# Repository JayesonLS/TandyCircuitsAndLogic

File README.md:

TandyCircuitsAndLogic
=====================

Circuits and programmable Logic for use with Tandy computers.

See the main source file (.pld for WinCUPL projects) in each folder for 
specific details. Check that the compiled file (.jed) is up to date
(committed at the same time or later than the most recent source changes)
before programming.

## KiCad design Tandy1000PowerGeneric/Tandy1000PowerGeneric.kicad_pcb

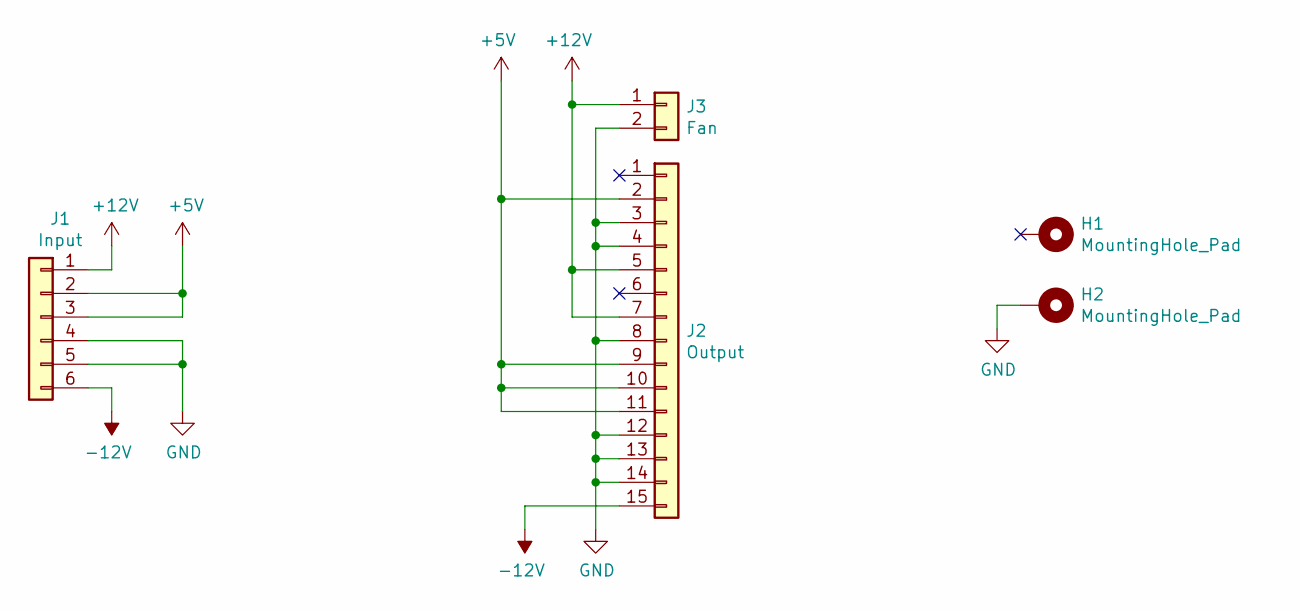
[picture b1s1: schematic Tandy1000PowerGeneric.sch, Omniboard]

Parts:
H1, H2: MountingHole_Pad; MountingHole_3.7mm_Pad
J1: Input; Molex5273Header_6
J2: Output; Molex5273Header_15
J3: Fan; FanConnector2Pin

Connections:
+5V: J1.2, J1.3, J2.2, J2.9, J2.10, J2.11
+12V: J1.1, J2.5, J2.7, J3.1
-12V: J1.6, J2.15
GND: H2.1, J1.4, J1.5, J2.3, J2.4, J2.8, J2.12, J2.13, J2.14, J3.2

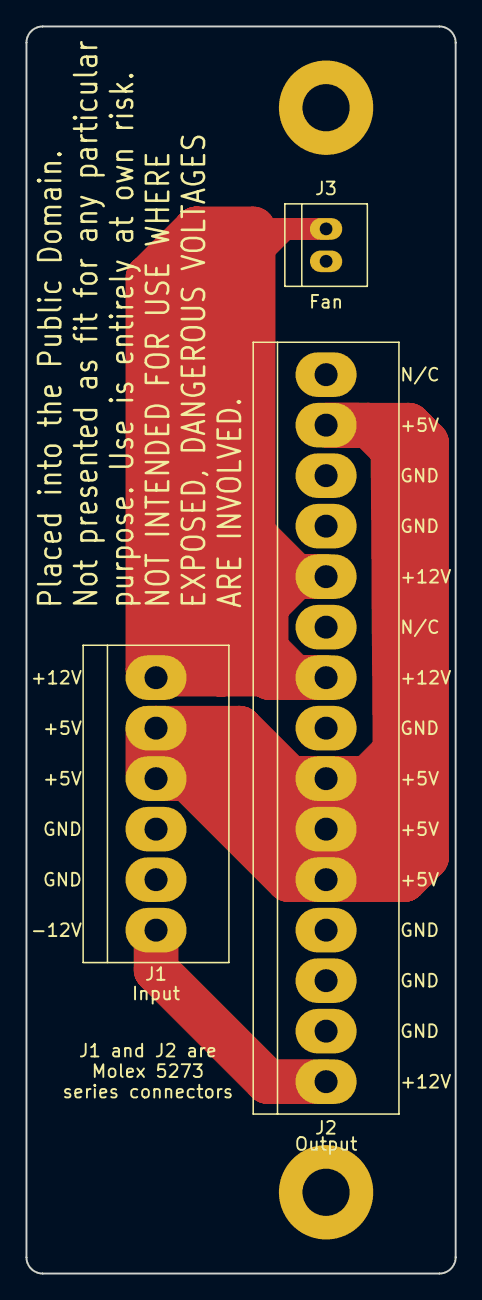
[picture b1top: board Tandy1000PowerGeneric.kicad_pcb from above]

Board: 2 copper layers, 33.7 x 97.8 mm, 5 parts (0 on the bottom side), 4 nets.

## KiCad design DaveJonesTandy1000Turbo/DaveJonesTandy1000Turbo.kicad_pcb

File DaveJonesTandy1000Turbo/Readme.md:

Original design by David Jones and published in Electronics Australia. 

This KiCad project and board layout by Jayeson Lee-Steere and placed in the public domain.

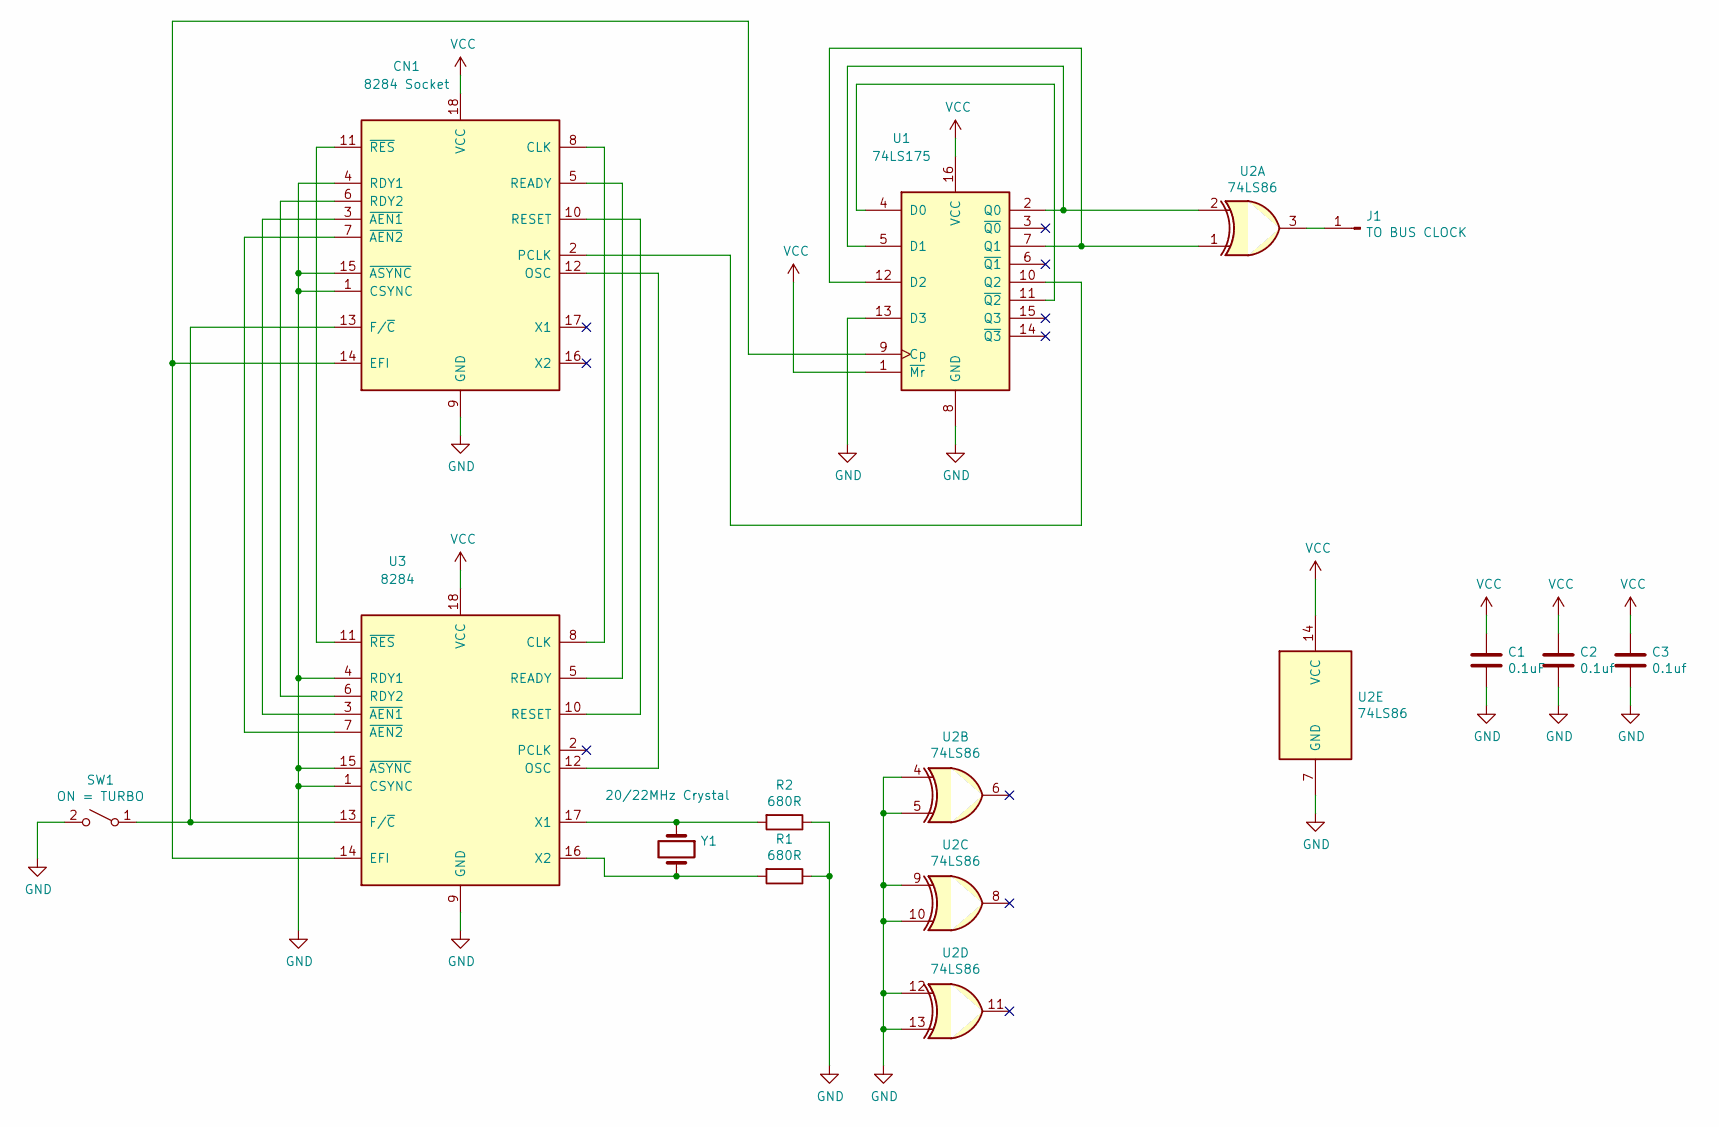
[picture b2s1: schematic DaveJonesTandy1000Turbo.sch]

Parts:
C1: 0.1uF; C_Disc_D8.0mm_W5.0mm_P5.00mm
C2, C3: 0.1uf; C_Disc_D8.0mm_W5.0mm_P5.00mm
CN1: 8284 Socket; DIP-18_W7.62mm_Socket
J1: TO BUS CLOCK; TestPoint_THTPad_D2.0mm_Drill1.0mm
R1, R2: 680R; R_Axial_DIN0207_L6.3mm_D2.5mm_P10.16mm_Horizontal
SW1: ON = TURBO; TestPoint_2Pads_Pitch5.08mm_Drill1.3mm
U1: 74LS175; DIP-16_W7.62mm_Socket
U2: 74LS86; DIP-14_W7.62mm_Socket
U3: 8284; DIP-18_W7.62mm_Socket
Y1: 20/22MHz Crystal; Crystal_HC49-U_Vertical

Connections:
GND: C1.2, C2.2, C3.2, CN1.1 (CSYNC), CN1.4 (RDY1), CN1.9 (GND), CN1.15 (~ASYNC~), R1.1, R2.1, SW1.2 (B), U1.8 (GND), U1.13 (D3), U2.4, U2.5, U2.7 (GND), U2.9, U2.10, U2.12, U2.13, U3.1 (CSYNC), U3.4 (RDY1), U3.9 (GND), U3.15 (~ASYNC~)
unnamed: CN1.2 (PCLK), U1.10 (Q2)
unnamed: CN1.3 (~AEN1~), U3.3 (~AEN1~)
unnamed: CN1.5 (READY), U3.5 (READY)
unnamed: CN1.6 (RDY2), U3.6 (RDY2)
unnamed: CN1.7 (~AEN2~), U3.7 (~AEN2~)
unnamed: CN1.8 (CLK), U3.8 (CLK)
unnamed: CN1.10 (RESET), U3.10 (RESET)
unnamed: CN1.11 (~RES~), U3.11 (~RES~)
unnamed: CN1.12 (OSC), U3.12 (OSC)
unnamed: CN1.13 (F/~C~), SW1.1 (A), U3.13 (F/~C~)
unnamed: CN1.14 (EFI), U1.9 (Cp), U3.14 (EFI)
unnamed: J1.1, U2.3
unnamed: R1.2, U3.16 (X2), Y1.2
unnamed: R2.2, U3.17 (X1), Y1.1
unnamed: U1.2 (Q0), U1.5 (D1), U2.2
unnamed: U1.4 (D0), U1.11 (~Q2)
unnamed: U1.7 (Q1), U1.12 (D2), U2.1
VCC: C1.1, C2.1, C3.1, CN1.18 (VCC), U1.1 (~Mr), U1.16 (VCC), U2.14 (VCC), U3.18 (VCC)

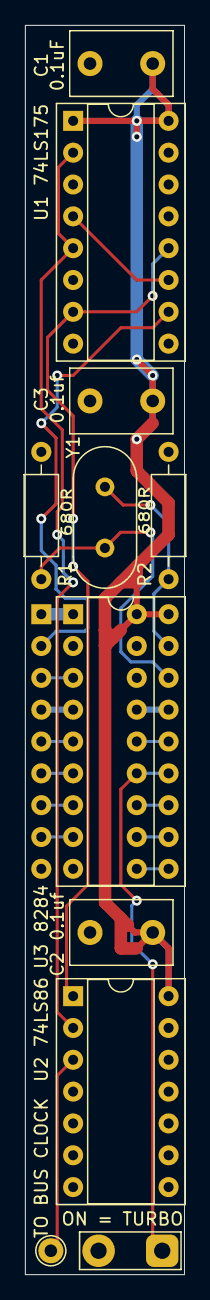
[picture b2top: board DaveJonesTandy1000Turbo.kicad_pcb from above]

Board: 2 copper layers, 12.7 x 99.7 mm, 12 parts (0 on the bottom side), 19 nets.

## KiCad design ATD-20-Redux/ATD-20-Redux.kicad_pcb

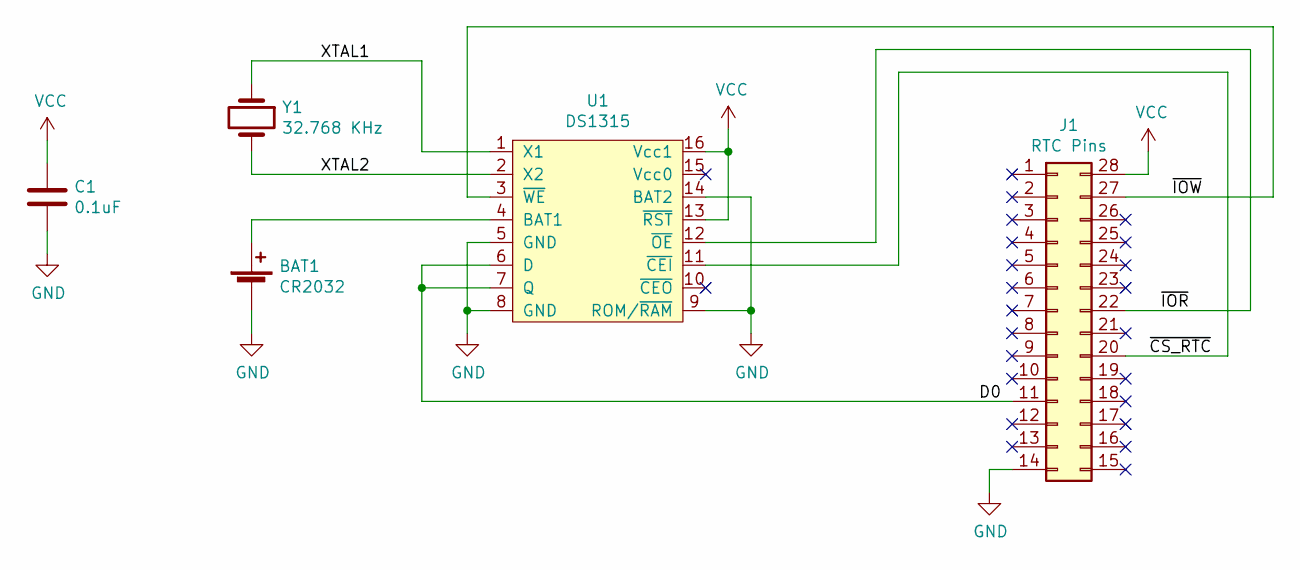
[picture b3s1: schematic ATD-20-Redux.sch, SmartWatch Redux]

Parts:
BAT1: CR2032; BatteryHolder_Keystone_103_1x20mm
C1: 0.1uF; C_Disc_D4.3mm_W1.9mm_P5.00mm
J1: RTC Pins; DIP-28_W15.24mm_Socket
U1: DS1315; DIP-16_W7.62mm
Y1: 32.768 KHz; Crystal_C38-LF_D3.0mm_L8.0mm_Horizontal

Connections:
/D0: J1.11, U1.6 (D), U1.7 (Q)
/XTAL1: U1.1 (X1), Y1.1
/XTAL2: U1.2 (X2), Y1.2
/~CS_RTC: J1.20, U1.11 (~CEI)
/~IOR: J1.22, U1.12 (~OE)
/~IOW: J1.27, U1.3 (~WE)
GND: BAT1.2 (-), C1.2, J1.14, U1.5 (GND), U1.8 (GND), U1.9 (ROM/~RAM), U1.14 (BAT2)
unnamed: BAT1.1 (+), U1.4 (BAT1)
VCC: C1.1, J1.28, U1.13 (~RST), U1.16 (Vcc1)

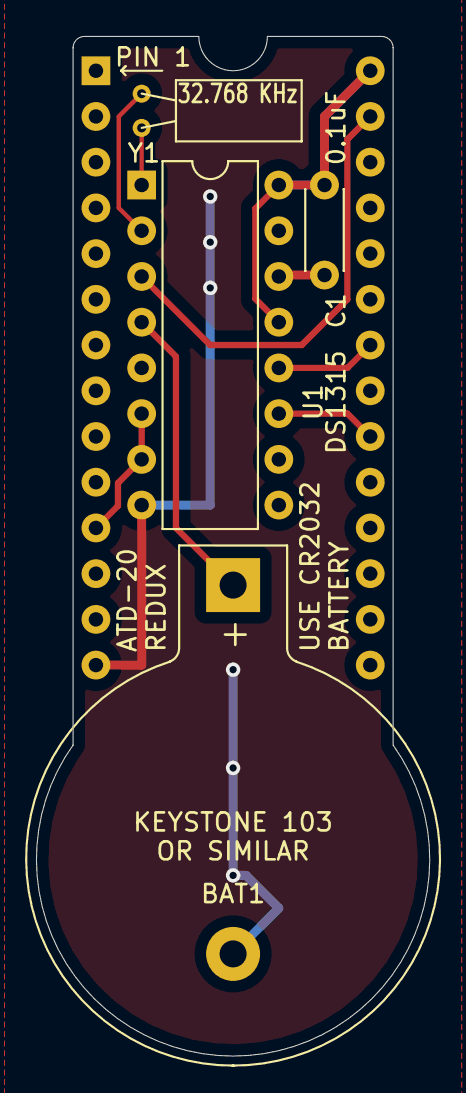
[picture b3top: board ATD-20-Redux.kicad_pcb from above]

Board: 2 copper layers, 21.8 x 56.6 mm, 5 parts (0 on the bottom side), 9 nets.

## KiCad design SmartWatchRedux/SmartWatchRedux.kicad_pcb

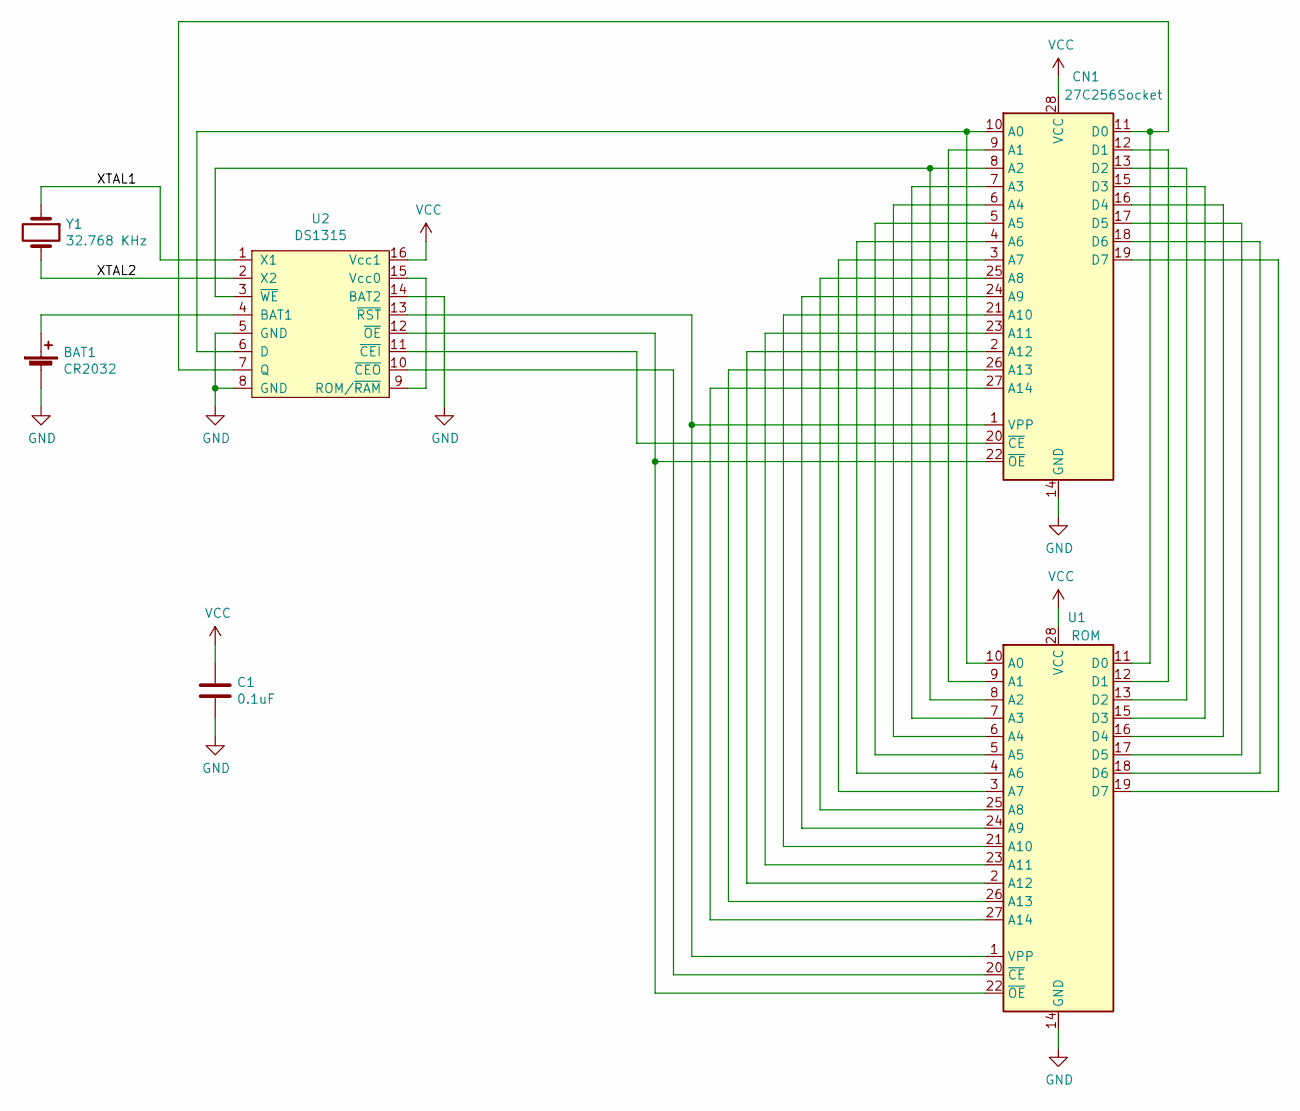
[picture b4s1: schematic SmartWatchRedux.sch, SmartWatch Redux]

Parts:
BAT1: CR2032; BatteryHolder_Keystone_103_1x20mm
C1: 0.1uF; C_0805_2012Metric_Pad1.18x1.45mm_HandSolder
CN1: 27C256Socket; DIP-28_W15.24mm
U1: ROM; DIP-28_W15.24mm_Socket
U2: DS1315; DIP-16_W7.62mm
Y1: 32.768 KHz; Crystal_C38-LF_D3.0mm_L8.0mm_Horizontal

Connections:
/XTAL1: U2.1 (X1), Y1.1
/XTAL2: U2.2 (X2), Y1.2
GND: BAT1.2 (-), C1.2, CN1.14 (GND), U1.14 (GND), U2.5 (GND), U2.8 (GND), U2.14 (BAT2)
unnamed: BAT1.1 (+), U2.4 (BAT1)
unnamed: CN1.1 (VPP), U1.1 (VPP), U2.13 (~RST)
unnamed: CN1.2 (A12), U1.2 (A12)
unnamed: CN1.3 (A7), U1.3 (A7)
unnamed: CN1.4 (A6), U1.4 (A6)
unnamed: CN1.5 (A5), U1.5 (A5)
unnamed: CN1.6 (A4), U1.6 (A4)
unnamed: CN1.7 (A3), U1.7 (A3)
unnamed: CN1.8 (A2), U1.8 (A2), U2.3 (~WE)
unnamed: CN1.9 (A1), U1.9 (A1)
unnamed: CN1.10 (A0), U1.10 (A0), U2.6 (D)
unnamed: CN1.11 (D0), U1.11 (D0), U2.7 (Q)
unnamed: CN1.12 (D1), U1.12 (D1)
unnamed: CN1.13 (D2), U1.13 (D2)
unnamed: CN1.15 (D3), U1.15 (D3)
unnamed: CN1.16 (D4), U1.16 (D4)
unnamed: CN1.17 (D5), U1.17 (D5)
unnamed: CN1.18 (D6), U1.18 (D6)
unnamed: CN1.19 (D7), U1.19 (D7)
unnamed: CN1.20 (~CE), U2.11 (~CEI)
unnamed: CN1.21 (A10), U1.21 (A10)
unnamed: CN1.22 (~OE), U1.22 (~OE), U2.12 (~OE)
unnamed: CN1.23 (A11), U1.23 (A11)
unnamed: CN1.24 (A9), U1.24 (A9)
unnamed: CN1.25 (A8), U1.25 (A8)
unnamed: CN1.26 (A13), U1.26 (A13)
unnamed: CN1.27 (A14), U1.27 (A14)
unnamed: U1.20 (~CE), U2.10 (~CEO)
unnamed: U2.9 (ROM/~RAM), U2.15 (Vcc0)
VCC: C1.1, CN1.28 (VCC), U1.28 (VCC), U2.16 (Vcc1)

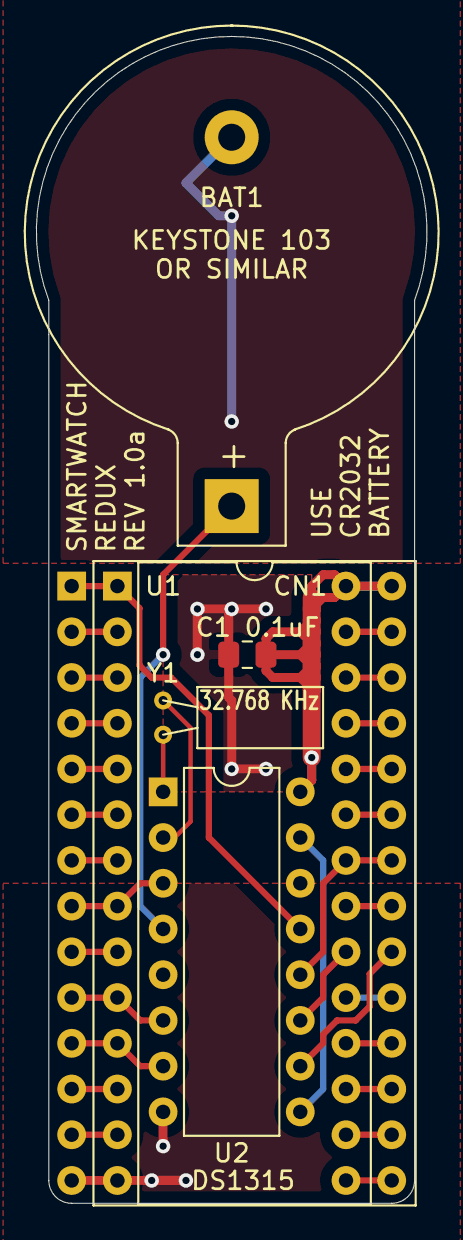
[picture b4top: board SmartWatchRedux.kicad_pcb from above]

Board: 2 copper layers, 21.7 x 64.8 mm, 6 parts (0 on the bottom side), 33 nets.

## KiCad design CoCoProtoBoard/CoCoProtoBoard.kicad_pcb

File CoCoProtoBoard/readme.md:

CoCo Prototyping Board
======================

This is a basic prototyping board for the Color Computer cartridge port.

Everything has been entered into the public domain so feel free to make them, 
sell them, modify the design, or use the board outline in your own CoCo
designs.

The board has been sized to the 100mm x 100mm size that is the limit for very
low cost board production at some PCB vendors. For prototyping purposes, the
lead free HASL finish will typically leave you with very nicely tinned fingers
on the edge connector. An ENIG finish is not recommended - the gold plate is
extremely thin and will wear off very quickly. Hard gold plated fingers is 
fine, however likely overkill for prototypes.

Gerbers are provided in the Gerbers folder.

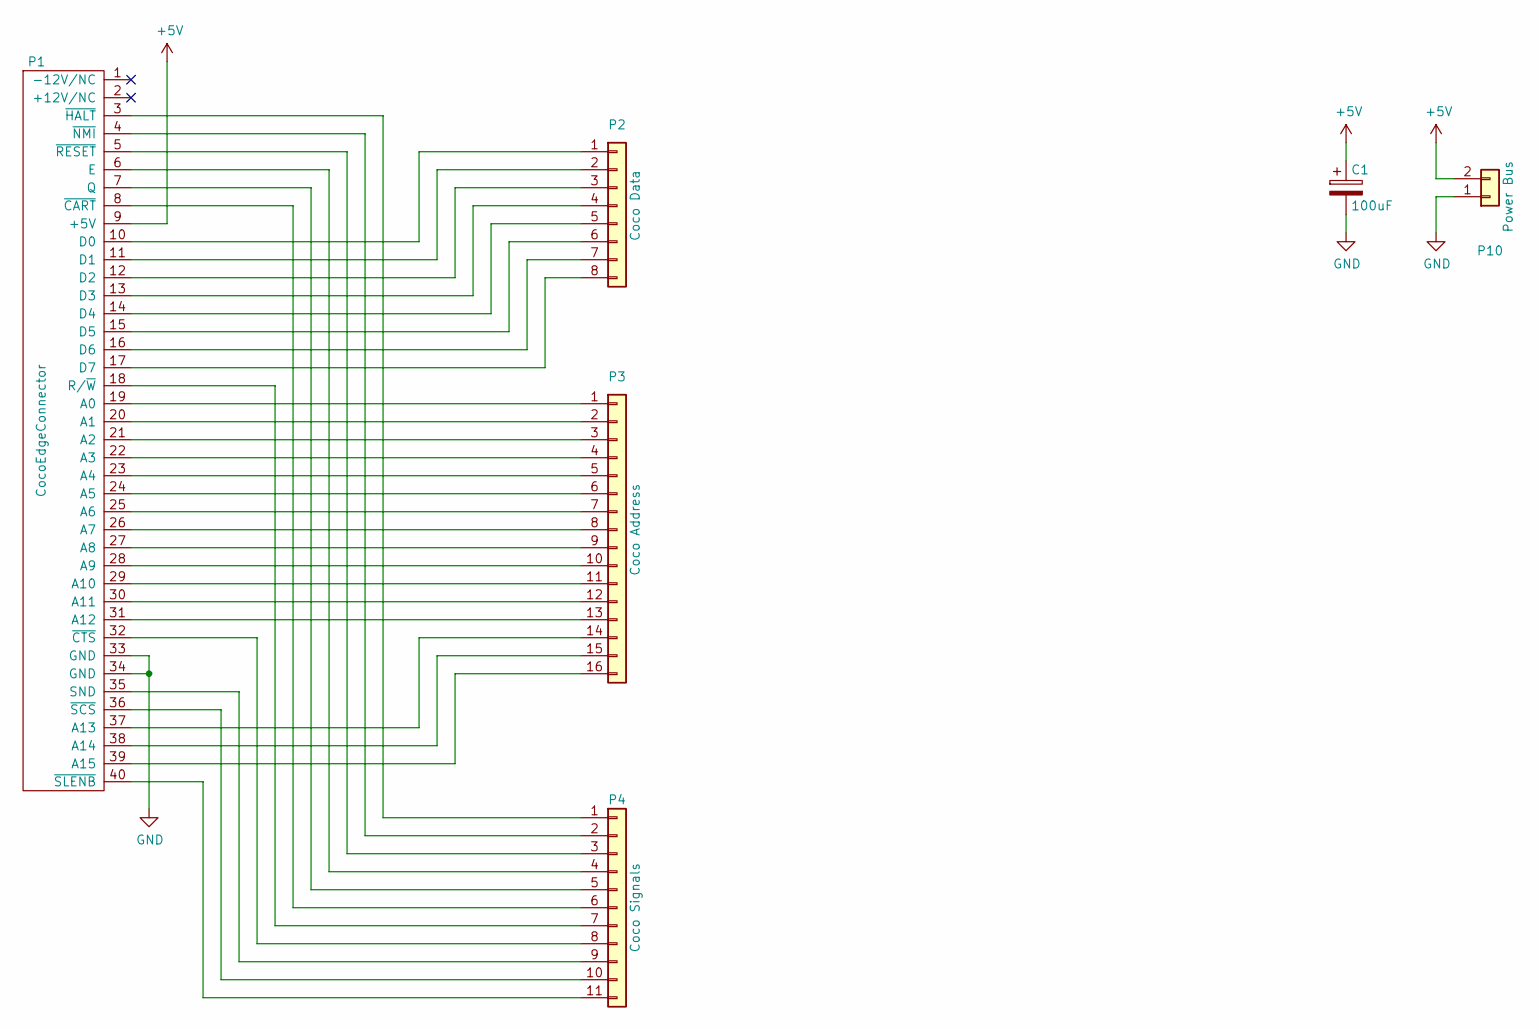
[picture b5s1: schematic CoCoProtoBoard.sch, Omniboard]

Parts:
C1: 100uF; C_Radial_D7.5_L11.2_P2.5
P1: CocoEdgeConnector; CocoCardEdge
P2: Coco Data; DIP-16_W7.62mm
P3: Coco Address; DIP-32_W15.24mm
P4: Coco Signals; DIP-22_W10.16mm
P10: Power Bus; DIP-16_W7.62mm

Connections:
+5V: C1.1, P1.9 (+5V), P10.2
GND: C1.2, P1.33 (GND), P1.34 (GND), P10.1
unnamed: P1.3 (~HALT), P4.1
unnamed: P1.4 (~NMI), P4.2
unnamed: P1.5 (~RESET), P4.3
unnamed: P1.6 (E), P4.4
unnamed: P1.7 (Q), P4.5
unnamed: P1.8 (~CART), P4.6
unnamed: P1.10 (D0), P2.1
unnamed: P1.11 (D1), P2.2
unnamed: P1.12 (D2), P2.3
unnamed: P1.13 (D3), P2.4
unnamed: P1.14 (D4), P2.5
unnamed: P1.15 (D5), P2.6
unnamed: P1.16 (D6), P2.7
unnamed: P1.17 (D7), P2.8
unnamed: P1.18 (R/~W), P4.7
unnamed: P1.19 (A0), P3.1
unnamed: P1.20 (A1), P3.2
unnamed: P1.21 (A2), P3.3
unnamed: P1.22 (A3), P3.4
unnamed: P1.23 (A4), P3.5
unnamed: P1.24 (A5), P3.6
unnamed: P1.25 (A6), P3.7
unnamed: P1.26 (A7), P3.8
unnamed: P1.27 (A8), P3.9
unnamed: P1.28 (A9), P3.10
unnamed: P1.29 (A10), P3.11
unnamed: P1.30 (A11), P3.12
unnamed: P1.31 (A12), P3.13
unnamed: P1.32 (~CTS), P4.8
unnamed: P1.35 (SND), P4.9
unnamed: P1.36 (~SCS), P4.10
unnamed: P1.37 (A13), P3.14
unnamed: P1.38 (A14), P3.15
unnamed: P1.39 (A15), P3.16
unnamed: P1.40 (~SLENB), P4.11

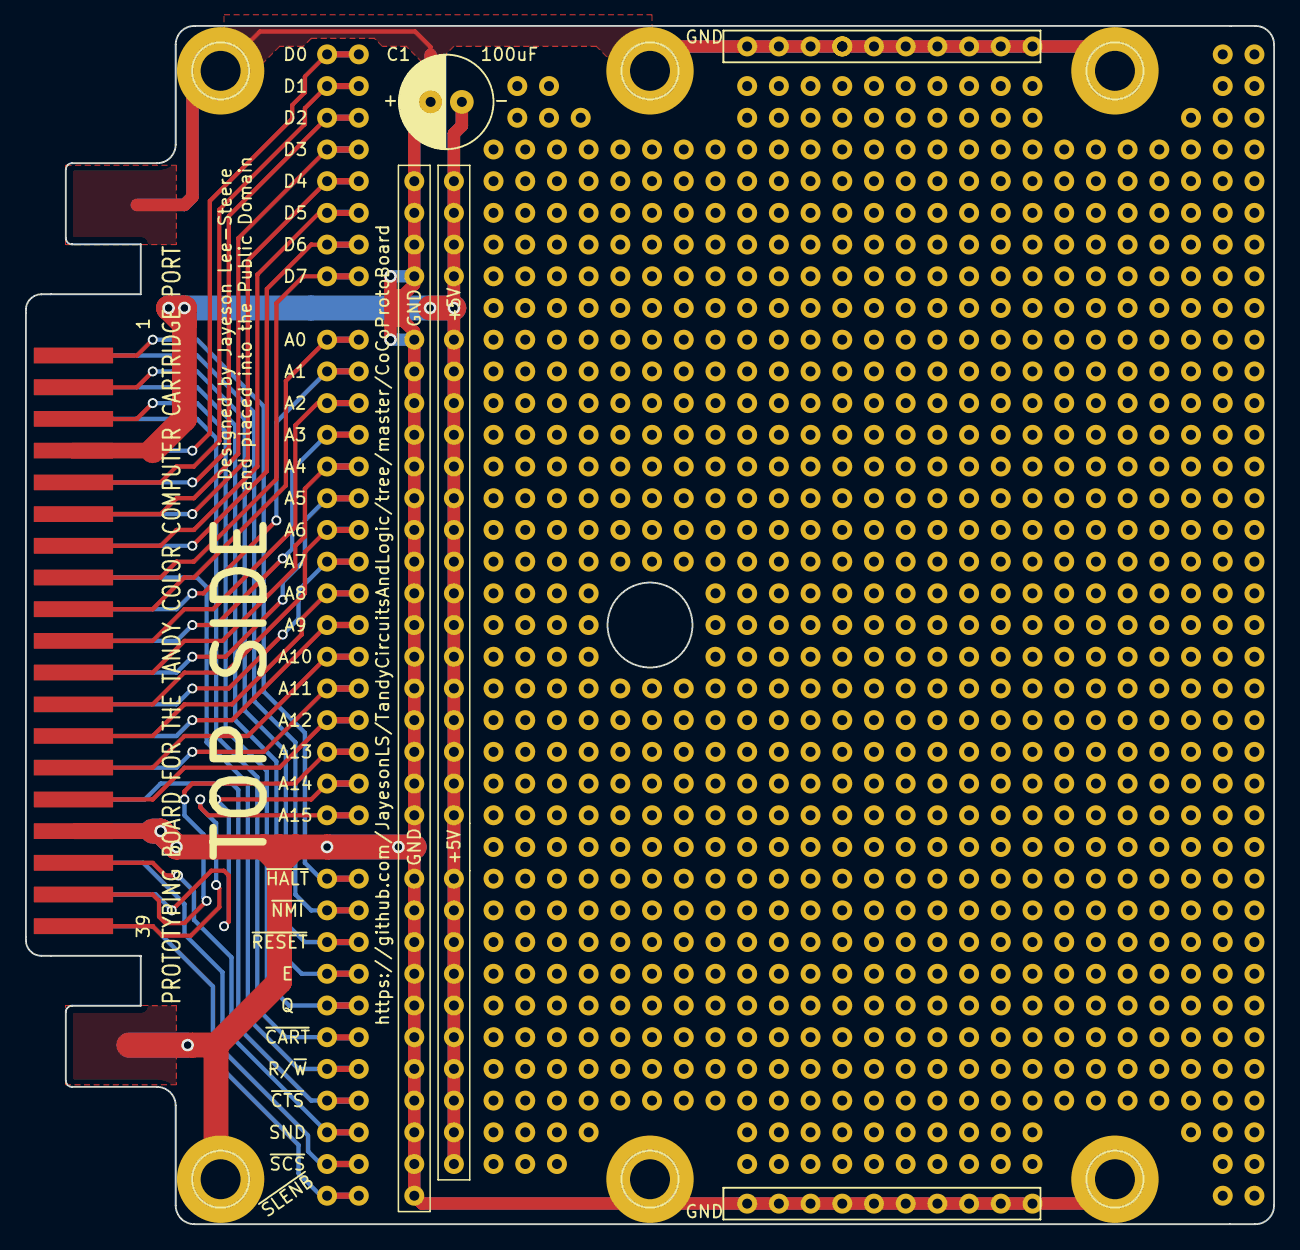
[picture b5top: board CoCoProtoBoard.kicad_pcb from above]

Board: 2 copper layers, 100.0 x 96.0 mm, 6 parts (0 on the bottom side), 37 nets.

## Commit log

2016-05-15 Update readme and license.
2016-05-15 First pass at Coco 1/2 Improved color burst logic. Uses 16v8 GAL.
2016-05-15 Add a note to ImprovedColorBurst.
2016-05-15 Add more notes to ImprovedColorBurst.pld.
2021-01-24 Change repository from Coco specific projects to one to place any Tandy computer programmable logic.
2021-01-26 Initial pass of Tandy 1000 PAL for U53. Almost certainly has errors right now and needs results checking against a real Tandy PAL chip.
2021-01-29 Update README.md
    Rename for circuits as well as programmable logic.
2021-01-29 Update LICENSE
    Modify license to better cover non-software items.
2021-01-29 Initial WIP on Dave Jones Tandy 1000 Turbo.
2021-01-29 Intial circuit board layout pass done. Still completely untested at this point.
2021-02-08 Add board render image.
2021-02-08 Add image of board render to PNG.
2021-02-15 Initial pass at SmartWatch layout.
2021-02-16 Relocate crystal to be above DS1315 and closer to X1/X2 pins
2021-02-16 Add title to schematic.
2021-02-16 Ass SmartWatchRedux gerbers,
2021-02-16 Add Gerbers to DaveJonesTandy1000Turbo.
2021-02-19 Update to DaveJonesTurbo pcb
2021-02-19 First pass at CocoProtoBoard.
2021-02-19 Add renders of board.
2021-02-19 CocoProtoBoard: Swap +5v and GND rails and other minor tweaks.
2021-02-21 Update png of board and add gerbers.
2021-02-21 Add readme for CoCoProtoBoard.
2021-02-21 CoCoProtoBoard: Remove black border from render image.
2021-02-22 Additional silkscreen text and refinements.
2021-02-22 Update SmartWatchRedux Gerbers.
2021-03-10 Initial pass at ATD-20 Clock/Calendar Redux board.
2021-03-11 Refinements to SmartWatchRedux and ATD-20-Redux after assembling initial run of boards.
2021-03-11 Remove accidentally committed backup file.
2021-03-13 Minor changes to ATD-20-Redux.
2021-04-03 Remove SmartWatch projects as these have been moved to their own repository.
2021-05-18 Generate gerbes for DaveJonesTandy1000
2021-05-18 Tandy1000PowerGeneric: Add project including gerbers. Actually second revision - first had incorrect mounting hole spaceing, and was accidentally not committed.

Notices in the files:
CoCoProtoBoard/CoCoProtoBoard.kicad_pcb:
and placed into the Public Domain
DaveJonesTandy1000Turbo/DaveJonesTandy1000Turbo.kicad_pcb:
... and released into the public domain.
